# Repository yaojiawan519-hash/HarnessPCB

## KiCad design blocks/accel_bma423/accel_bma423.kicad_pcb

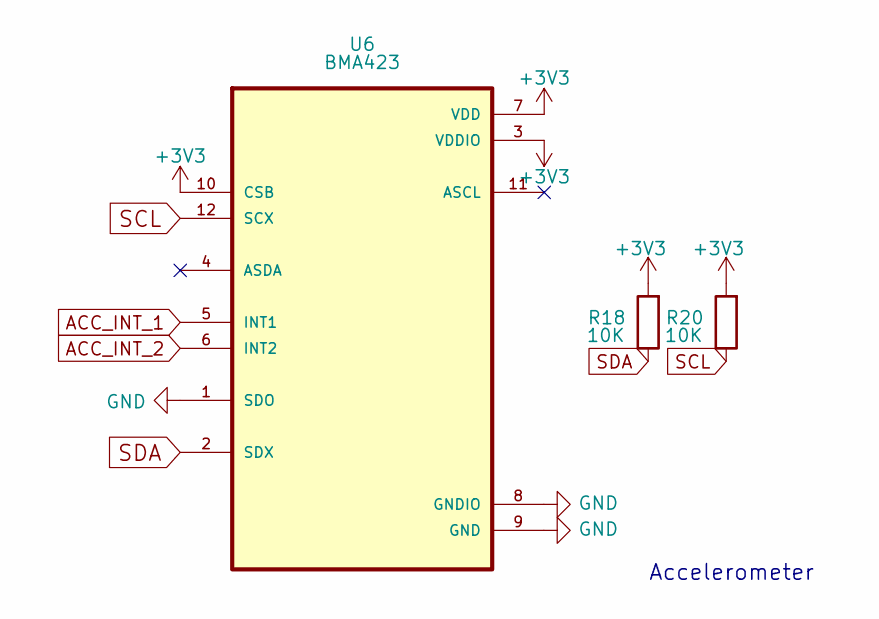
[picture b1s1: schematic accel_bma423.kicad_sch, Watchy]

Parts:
R18, R20: 10K; R_0402_1005Metric
U6: BMA423; LGA-12_2x2mm_P0.5mm

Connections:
+3V3: R18.2, R20.2, U6.3 (VDDIO), U6.7 (VDD), U6.10 (CSB)
ACC_INT_1: U6.5 (INT1)
ACC_INT_2: U6.6 (INT2)
GND: U6.1 (SDO), U6.8 (GNDIO), U6.9 (GND)
SCL: R20.1, U6.12 (SCX)
SDA: R18.1, U6.2 (SDX)

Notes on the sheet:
Accelerometer

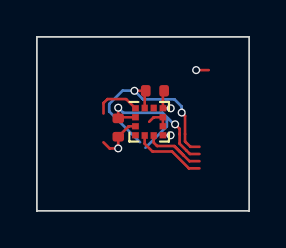
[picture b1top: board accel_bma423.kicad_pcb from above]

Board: 4 copper layers, 11.8 x 9.7 mm, 3 parts (0 on the bottom side), 4 nets.

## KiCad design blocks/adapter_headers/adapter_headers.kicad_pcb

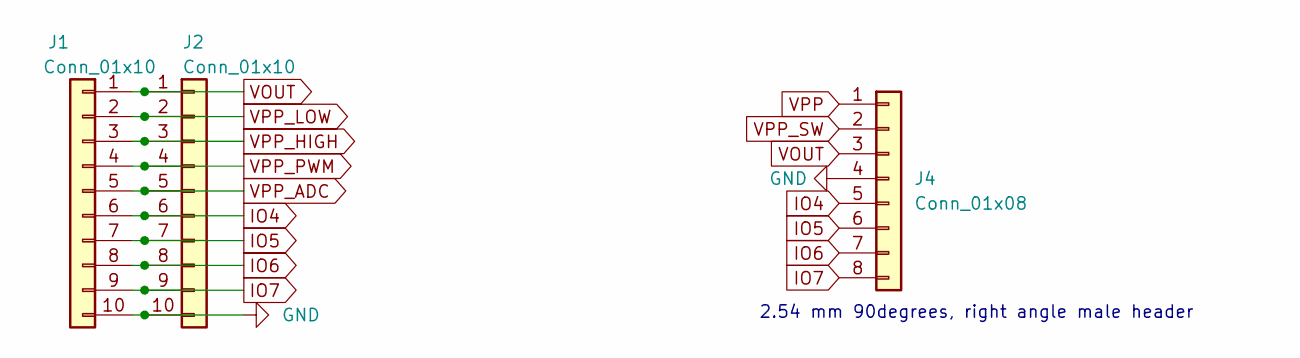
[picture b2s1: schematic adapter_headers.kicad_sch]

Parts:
J1: Conn_01x10; PinSocket_1x10_P2.54mm_Horizontal
J2: Conn_01x10; PinHeader_1x10_P2.54mm_Vertical
J4: Conn_01x08; PinHeader_1x08_P2.54mm_Horizontal

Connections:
GND: J1.10, J2.10, J4.4
IO4: J1.6, J2.6, J4.5
IO5: J1.7, J2.7, J4.6
IO6: J1.8, J2.8, J4.7
IO7: J1.9, J2.9, J4.8
VOUT: J1.1, J2.1, J4.3
VPP: J4.1
VPP_ADC: J1.5, J2.5
VPP_HIGH: J1.3, J2.3
VPP_LOW: J1.2, J2.2
VPP_PWM: J1.4, J2.4
VPP_SW: J4.2

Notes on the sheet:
2.54 mm 90degrees, right angle male header

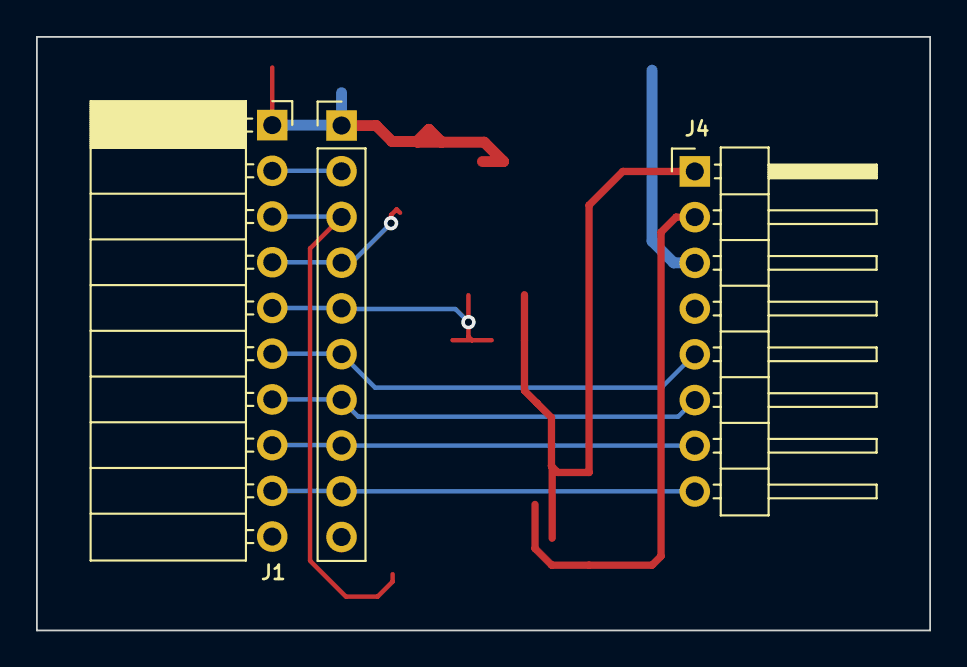
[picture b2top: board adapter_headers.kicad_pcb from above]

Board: 2 copper layers, 49.6 x 33.0 mm, 3 parts (0 on the bottom side), 10 nets.

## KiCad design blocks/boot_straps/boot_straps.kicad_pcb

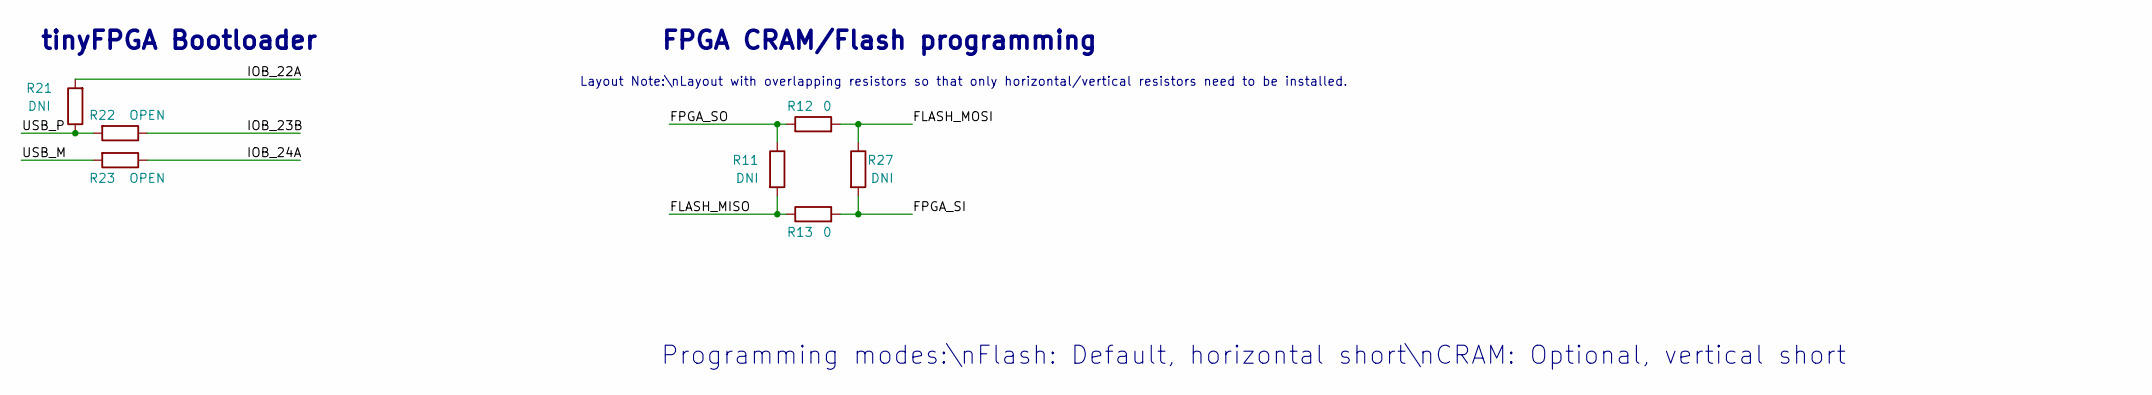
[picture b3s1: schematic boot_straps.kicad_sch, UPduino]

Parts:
R11, R21, R27: DNI; R_0603_1608Metric
R12, R13: 0; R_0603_1608Metric
R22, R23: OPEN; SolderJumper-2_0603_Open_TrianglePad1.0x1.5mm

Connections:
/FLASH_MISO: R11.2, R13.1
/FLASH_MOSI: R12.2, R27.1
/FPGA_SI: R13.2, R27.2
/FPGA_SO: R11.1, R12.1
/IOB_22A: R21.2
/IOB_23B: R22.1
/IOB_24A: R23.1
/USB_M: R23.2
/USB_P: R21.1, R22.2

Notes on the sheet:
Layout Note:\nLayout with overlapping resistors so that only horizontal/vertical resistors need to be installed.
Programming modes:\nFlash: Default, horizontal short\nCRAM: Optional, vertical short
tinyFPGA Bootloader
FPGA CRAM/Flash programming

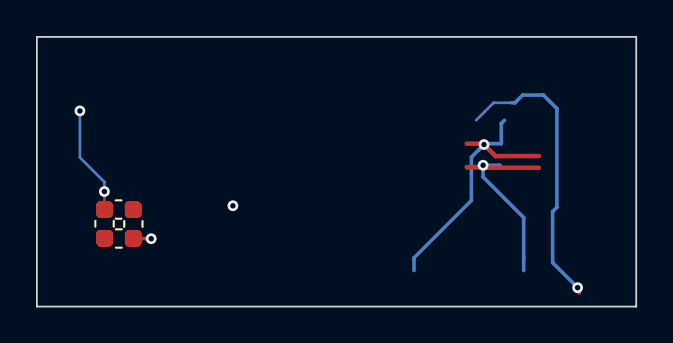
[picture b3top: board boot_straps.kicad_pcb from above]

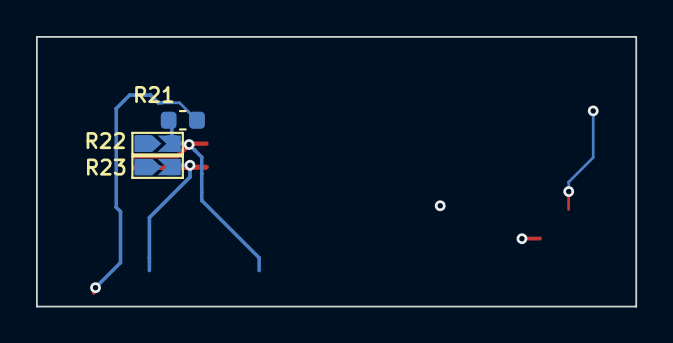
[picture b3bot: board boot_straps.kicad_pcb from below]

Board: 4 copper layers, 33.3 x 15.0 mm, 7 parts (3 on the bottom side), 5 nets.

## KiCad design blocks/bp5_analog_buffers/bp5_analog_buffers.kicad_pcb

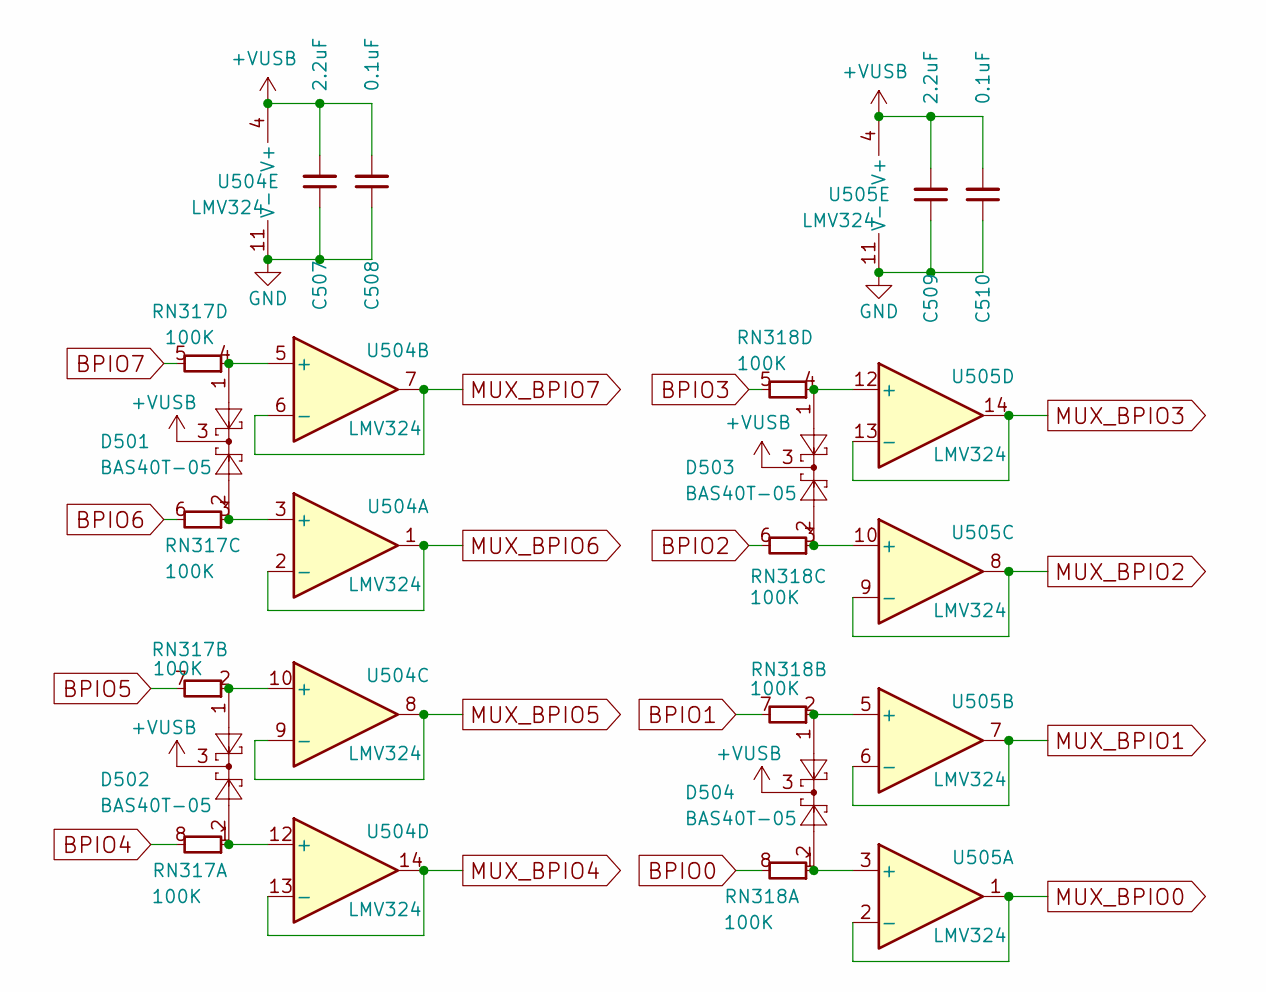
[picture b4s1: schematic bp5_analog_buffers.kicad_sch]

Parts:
C507, C509: 2.2uF; C_0402_1005Metric
C508, C510: 0.1uF; C_0402_1005Metric
D501, D502, D503, D504: BAS40T-05; SOT-523
RN317, RN318: 100K; R_Array_Convex_4x0402
U504, U505: LMV324; TSSOP-14_4.4x5mm_P0.65mm

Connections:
+VUSB: C507.2, C508.2, C509.2, C510.2, D501.3, D502.3, D503.3, D504.3, U504.4 (V+), U505.4 (V+)
BPIO0: RN318.8 (R1.8)
BPIO1: RN318.7 (R1.8)
BPIO2: RN318.6 (R1.8)
BPIO3: RN318.5 (R1.8)
BPIO4: RN317.8 (R1.8)
BPIO5: RN317.7 (R1.8)
BPIO6: RN317.6 (R1.8)
BPIO7: RN317.5 (R1.8)
GND: C507.1, C508.1, C509.1, C510.1, U504.11 (V-), U505.11 (V-)
MUX_BPIO0: U505.1, U505.2 (-)
MUX_BPIO1: U505.6 (-), U505.7
MUX_BPIO2: U505.8, U505.9 (-)
MUX_BPIO3: U505.13 (-), U505.14
MUX_BPIO4: U504.13 (-), U504.14
MUX_BPIO5: U504.8, U504.9 (-)
MUX_BPIO6: U504.1, U504.2 (-)
MUX_BPIO7: U504.6 (-), U504.7
unnamed: D502.2, RN317.1 (R1.1), U504.12 (+)
unnamed: D502.1, RN317.2 (R1.1), U504.10 (+)
unnamed: D501.2, RN317.3 (R1.1), U504.3 (+)
unnamed: D501.1, RN317.4 (R1.1), U504.5 (+)
unnamed: D504.2, RN318.1 (R1.1), U505.3 (+)
unnamed: D504.1, RN318.2 (R1.1), U505.5 (+)
unnamed: D503.2, RN318.3 (R1.1), U505.10 (+)
unnamed: D503.1, RN318.4 (R1.1), U505.12 (+)

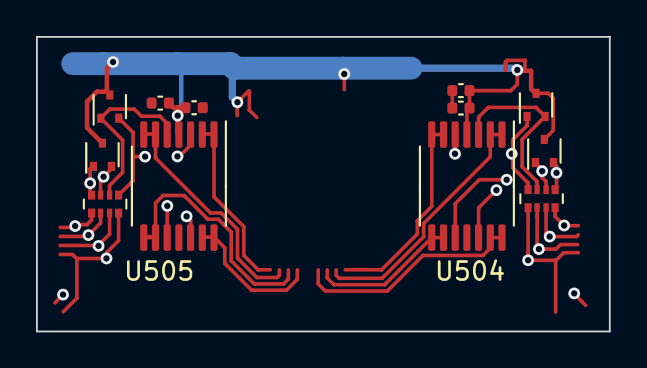
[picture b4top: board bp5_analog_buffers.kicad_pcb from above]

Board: 4 copper layers, 31.8 x 16.4 mm, 12 parts (0 on the bottom side), 18 nets.

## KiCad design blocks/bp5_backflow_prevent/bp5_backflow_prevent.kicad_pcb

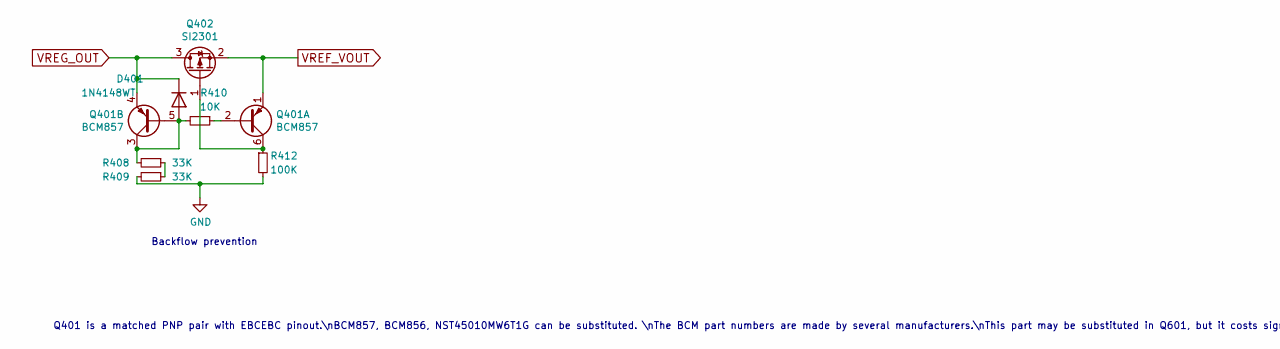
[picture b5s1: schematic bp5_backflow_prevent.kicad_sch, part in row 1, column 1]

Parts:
D401: 1N4148WT; D_SOD-523
Q401: BCM857; SOT-363_SC-70-6
Q402: SI2301; SOT-523
R408, R409: 33K; R_0402_1005Metric
R410: 10K; R_0402_1005Metric
R412: 100K; R_0402_1005Metric

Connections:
GND: R409.2, R412.2
unnamed: D401.2 (A), Q401.3 (C2), Q401.5 (B2), R408.2, R410.2
unnamed: Q401.2 (B1), R410.1
unnamed: Q401.6 (C1), Q402.1 (G), R412.1
unnamed: R408.1, R409.1
VREF_VOUT: Q401.1 (E1), Q402.2 (S)
VREG_OUT: D401.1 (K), Q401.4 (E2), Q402.3 (D)

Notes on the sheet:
Backflow prevention
Q401 is a matched PNP pair with EBCEBC pinout.\nBCM857, BCM856, NST45010MW6T1G can be substituted. \nThe BCM part numbers are made by several manufacturers.\nThis part may be substituted in Q601, but it costs significantly more.\n\nDMMT3906, PMP5201, PMP5501 are similar but have a BBCEEC pinout.\nT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

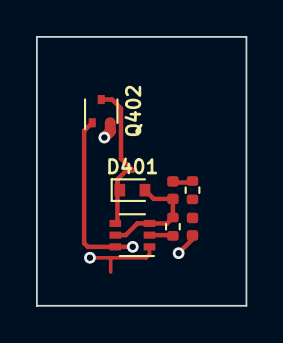
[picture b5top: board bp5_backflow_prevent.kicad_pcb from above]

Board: 4 copper layers, 11.6 x 14.9 mm, 7 parts (0 on the bottom side), 7 nets.

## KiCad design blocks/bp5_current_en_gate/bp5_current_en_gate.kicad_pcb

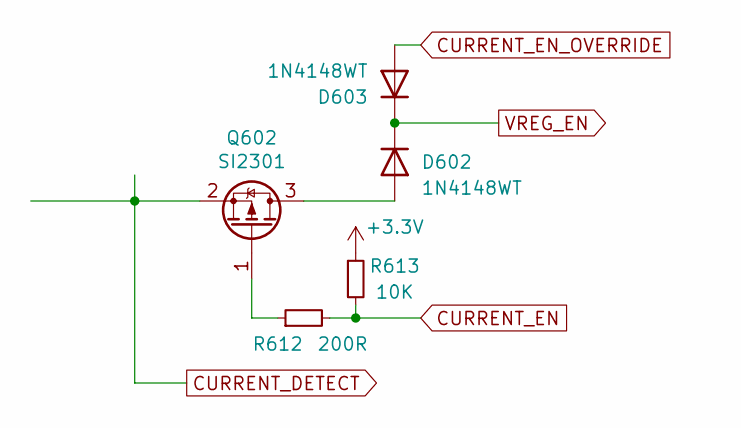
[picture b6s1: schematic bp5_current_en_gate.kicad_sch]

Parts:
D602, D603: 1N4148WT; D_SOD-523
Q602: SI2301; SOT-523
R612: 200R; R_0402_1005Metric
R613: 10K; R_0402_1005Metric

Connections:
+3V3: R613.1
CURRENT_DETECT: Q602.2 (S)
CURRENT_EN: R612.2, R613.2
CURRENT_EN_OVERRIDE: D603.2 (A)
unnamed: D602.2 (A), Q602.3 (D)
unnamed: Q602.1 (G), R612.1
VREG_EN: D602.1 (K), D603.1 (K)

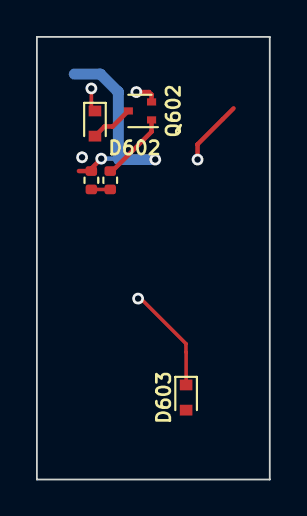
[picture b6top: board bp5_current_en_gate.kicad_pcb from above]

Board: 4 copper layers, 12.9 x 24.6 mm, 5 parts (0 on the bottom side), 4 nets.

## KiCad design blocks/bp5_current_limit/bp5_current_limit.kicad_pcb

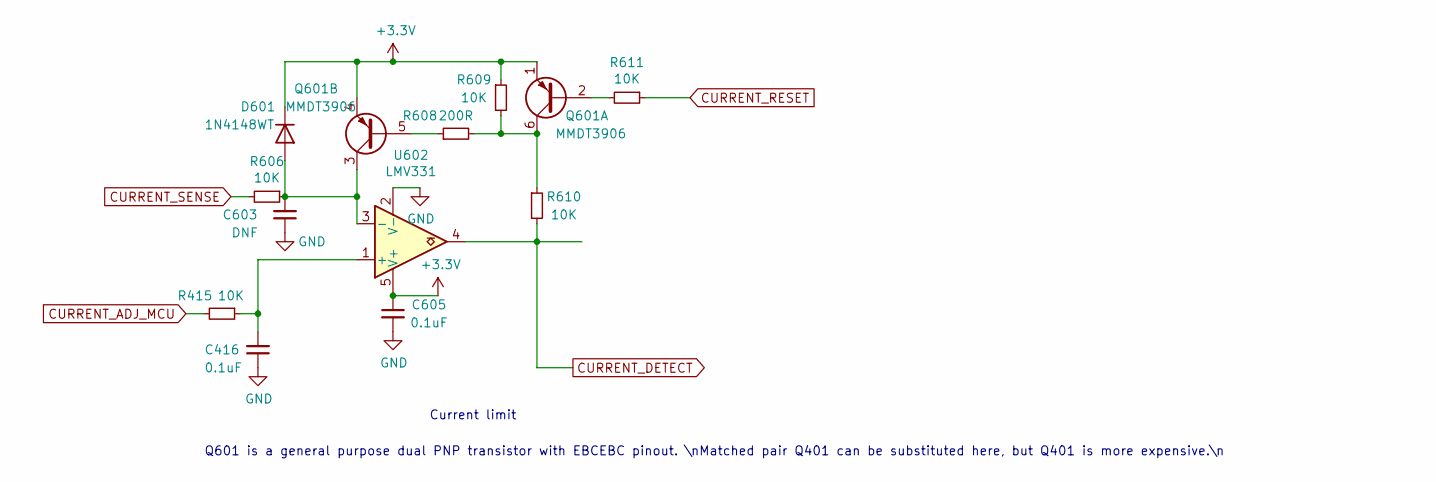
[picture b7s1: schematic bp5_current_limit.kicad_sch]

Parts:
C416, C605: 0.1uF; C_0402_1005Metric
C603: DNF; C_0402_1005Metric
D601: 1N4148WT; D_SOD-523
Q601: MMDT3906; SOT-363_SC-70-6
R415, R606, R609, R610, R611: 10K; R_0402_1005Metric
R608: 200R; R_0402_1005Metric
U602: LMV331; SOT-23-5

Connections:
+3V3: C605.1, D601.1 (K), Q601.1 (E1), Q601.4 (E2), R609.1, U602.5 (V+)
CURRENT_ADJ_MCU: R415.2
CURRENT_DETECT: R610.2, U602.4
CURRENT_RESET: R611.1
CURRENT_SENSE: R606.2
GND: C416.1, C603.1, C605.2, U602.2 (V-)
unnamed: C603.2, D601.2 (A), Q601.3 (C2), R606.1, U602.3 (-)
unnamed: Q601.2 (B1), R611.2
unnamed: Q601.6 (C1), R608.2, R609.2, R610.1
unnamed: Q601.5 (B2), R608.1
unnamed: C416.2, R415.1, U602.1 (+)

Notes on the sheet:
Current limit
Q601 is a general purpose dual PNP transistor with EBCEBC pinout. \nMatched pair Q401 can be substituted here, but Q401 is more expensive.\n

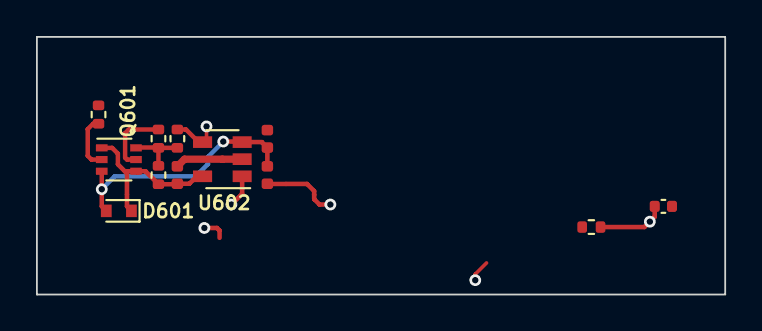
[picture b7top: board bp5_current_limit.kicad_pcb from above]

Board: 4 copper layers, 38.2 x 14.3 mm, 12 parts (0 on the bottom side), 8 nets.
